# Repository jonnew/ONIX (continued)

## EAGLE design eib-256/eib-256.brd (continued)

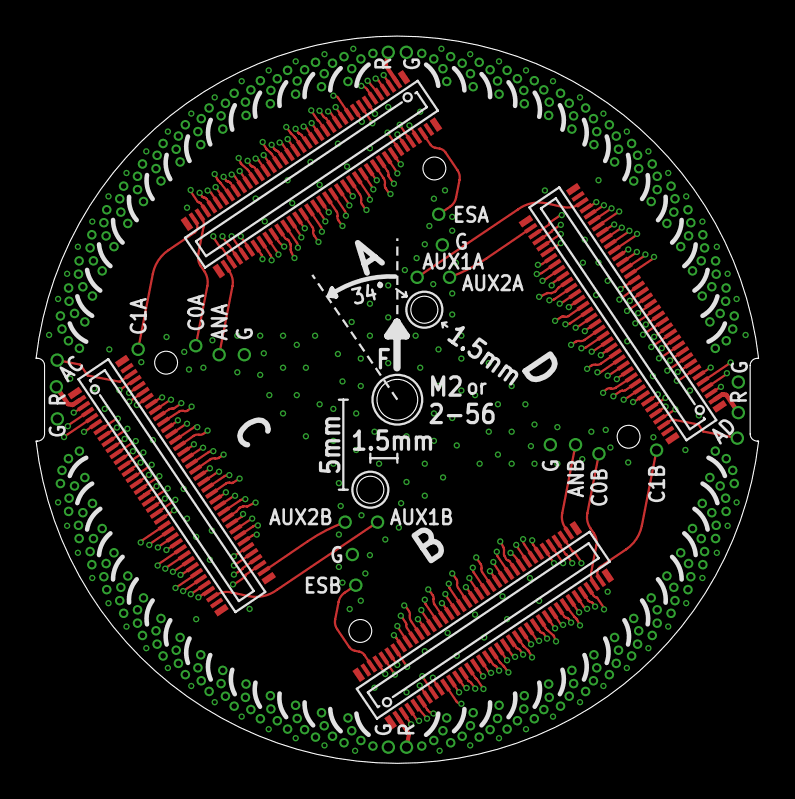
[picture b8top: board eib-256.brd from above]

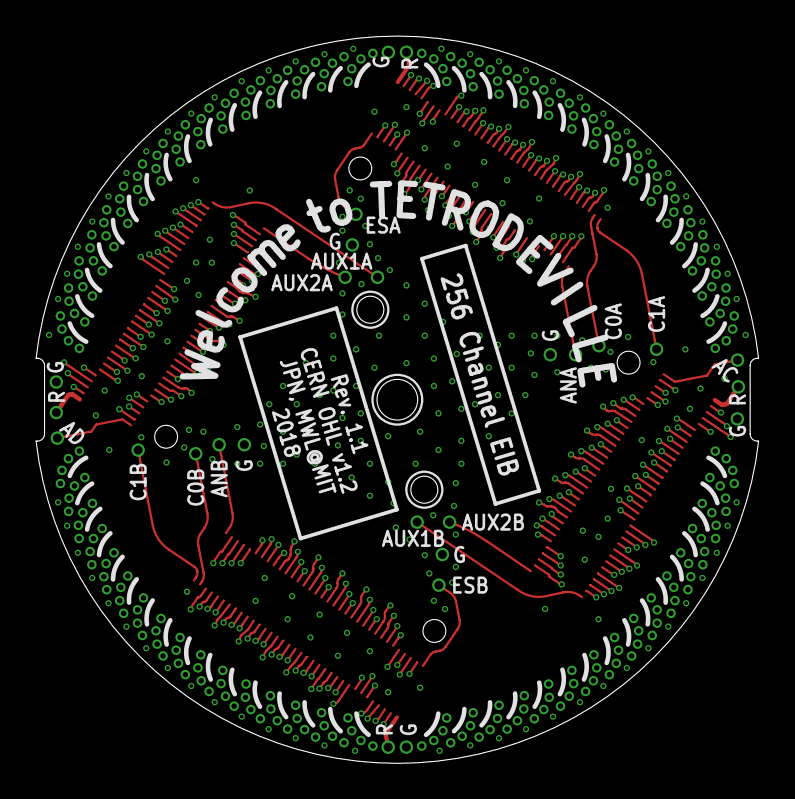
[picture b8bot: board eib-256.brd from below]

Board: 4 copper layers, 40.1 x 40.4 mm, 95 parts (32 on the bottom side), 275 nets.

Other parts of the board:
U$1: EIB_MOUNT_A
